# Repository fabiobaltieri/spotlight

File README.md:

# Spotlight

BLE enabled headlamp and mod boards.

## License (firmware, bootloader, ciq-app)

This program is free software: you can redistribute it and/or modify
it under the terms of the GNU General Public License as published by
the Free Software Foundation, either version 3 of the License, or
(at your option) any later version.

## License (hardware)

Hardware files are licensed under a
Creative Commons Attribution-ShareAlike 4.0 International License.

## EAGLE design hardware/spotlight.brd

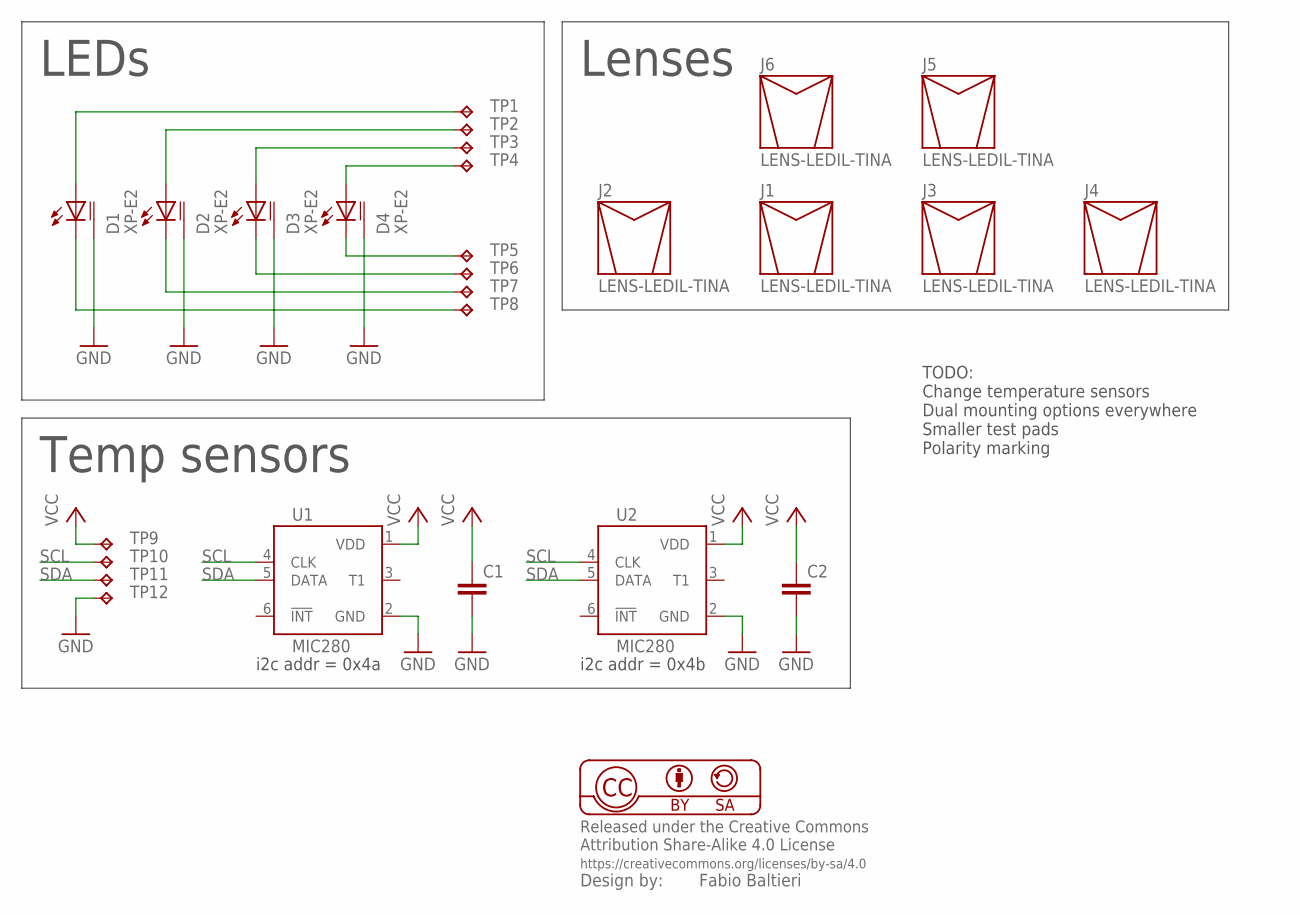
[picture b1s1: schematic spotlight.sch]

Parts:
C1, C2: C0603; 0603
D1, D2, D3, D4: XP-E2; CREE_XPE
J1, J2, J3, J4, J5, J6: LENS-LEDIL-TINA; LEDIL-TINA
TP1, TP2, TP3, TP4, TP5, TP6, TP7, TP8: TPTP18R; TP18R
TP9, TP10, TP11, TP12: TPTP14R; TP14R
U1, U2: MIC280; SOT23-6L

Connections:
GND: C1.2, C2.2, D1.TH, D2.TH, D3.TH, D4.TH, TP12.TP, U1.2 (GND), U2.2 (GND)
unnamed: D4.K (C), TP5.TP
unnamed: D3.K (C), TP6.TP
unnamed: D2.K (C), TP7.TP
unnamed: D1.K (C), TP8.TP
unnamed: D4.A, TP4.TP
unnamed: D3.A, TP3.TP
unnamed: D2.A, TP2.TP
unnamed: D1.A, TP1.TP
SCL: TP10.TP, U1.4 (CLK), U2.4 (CLK)
SDA: TP11.TP, U1.5 (DATA), U2.5 (DATA)
VCC: C1.1, C2.1, TP9.TP, U1.1 (VDD), U2.1 (VDD)

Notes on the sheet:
Lenses
LEDs
Temp sensors
i2c addr = 0x4a
i2c addr = 0x4b
TODO: Change temperature sensors Dual mounting options everywhere Smaller test pads Polarity marking

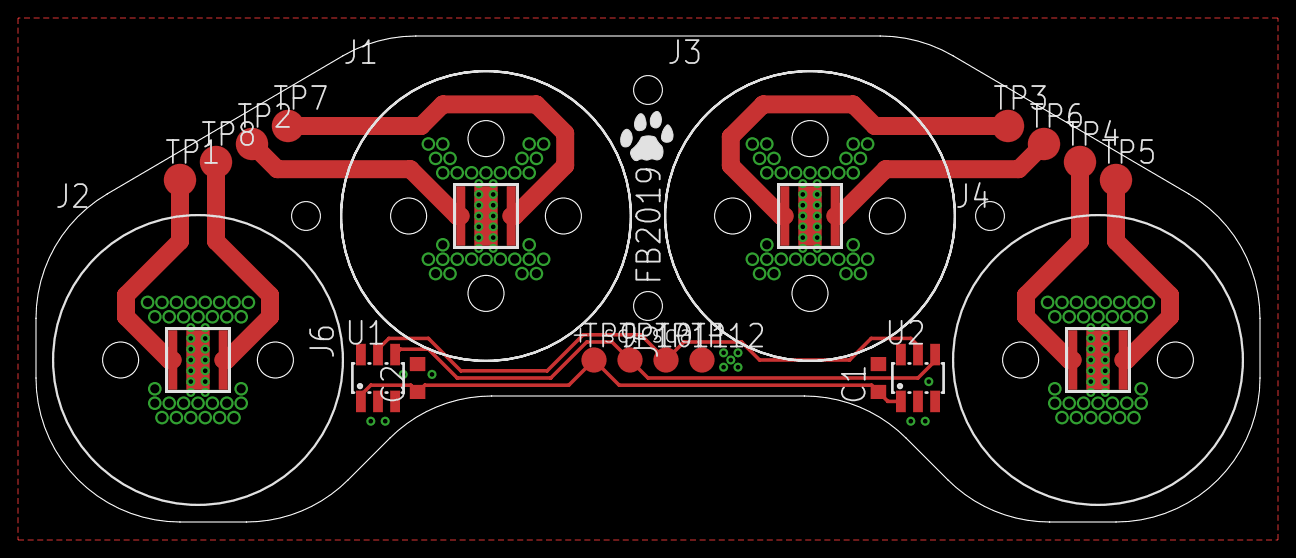
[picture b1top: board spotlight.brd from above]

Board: 2 copper layers, 68.0 x 27.0 mm, 27 parts (0 on the bottom side), 12 nets.

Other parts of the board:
U$1: CAT-L

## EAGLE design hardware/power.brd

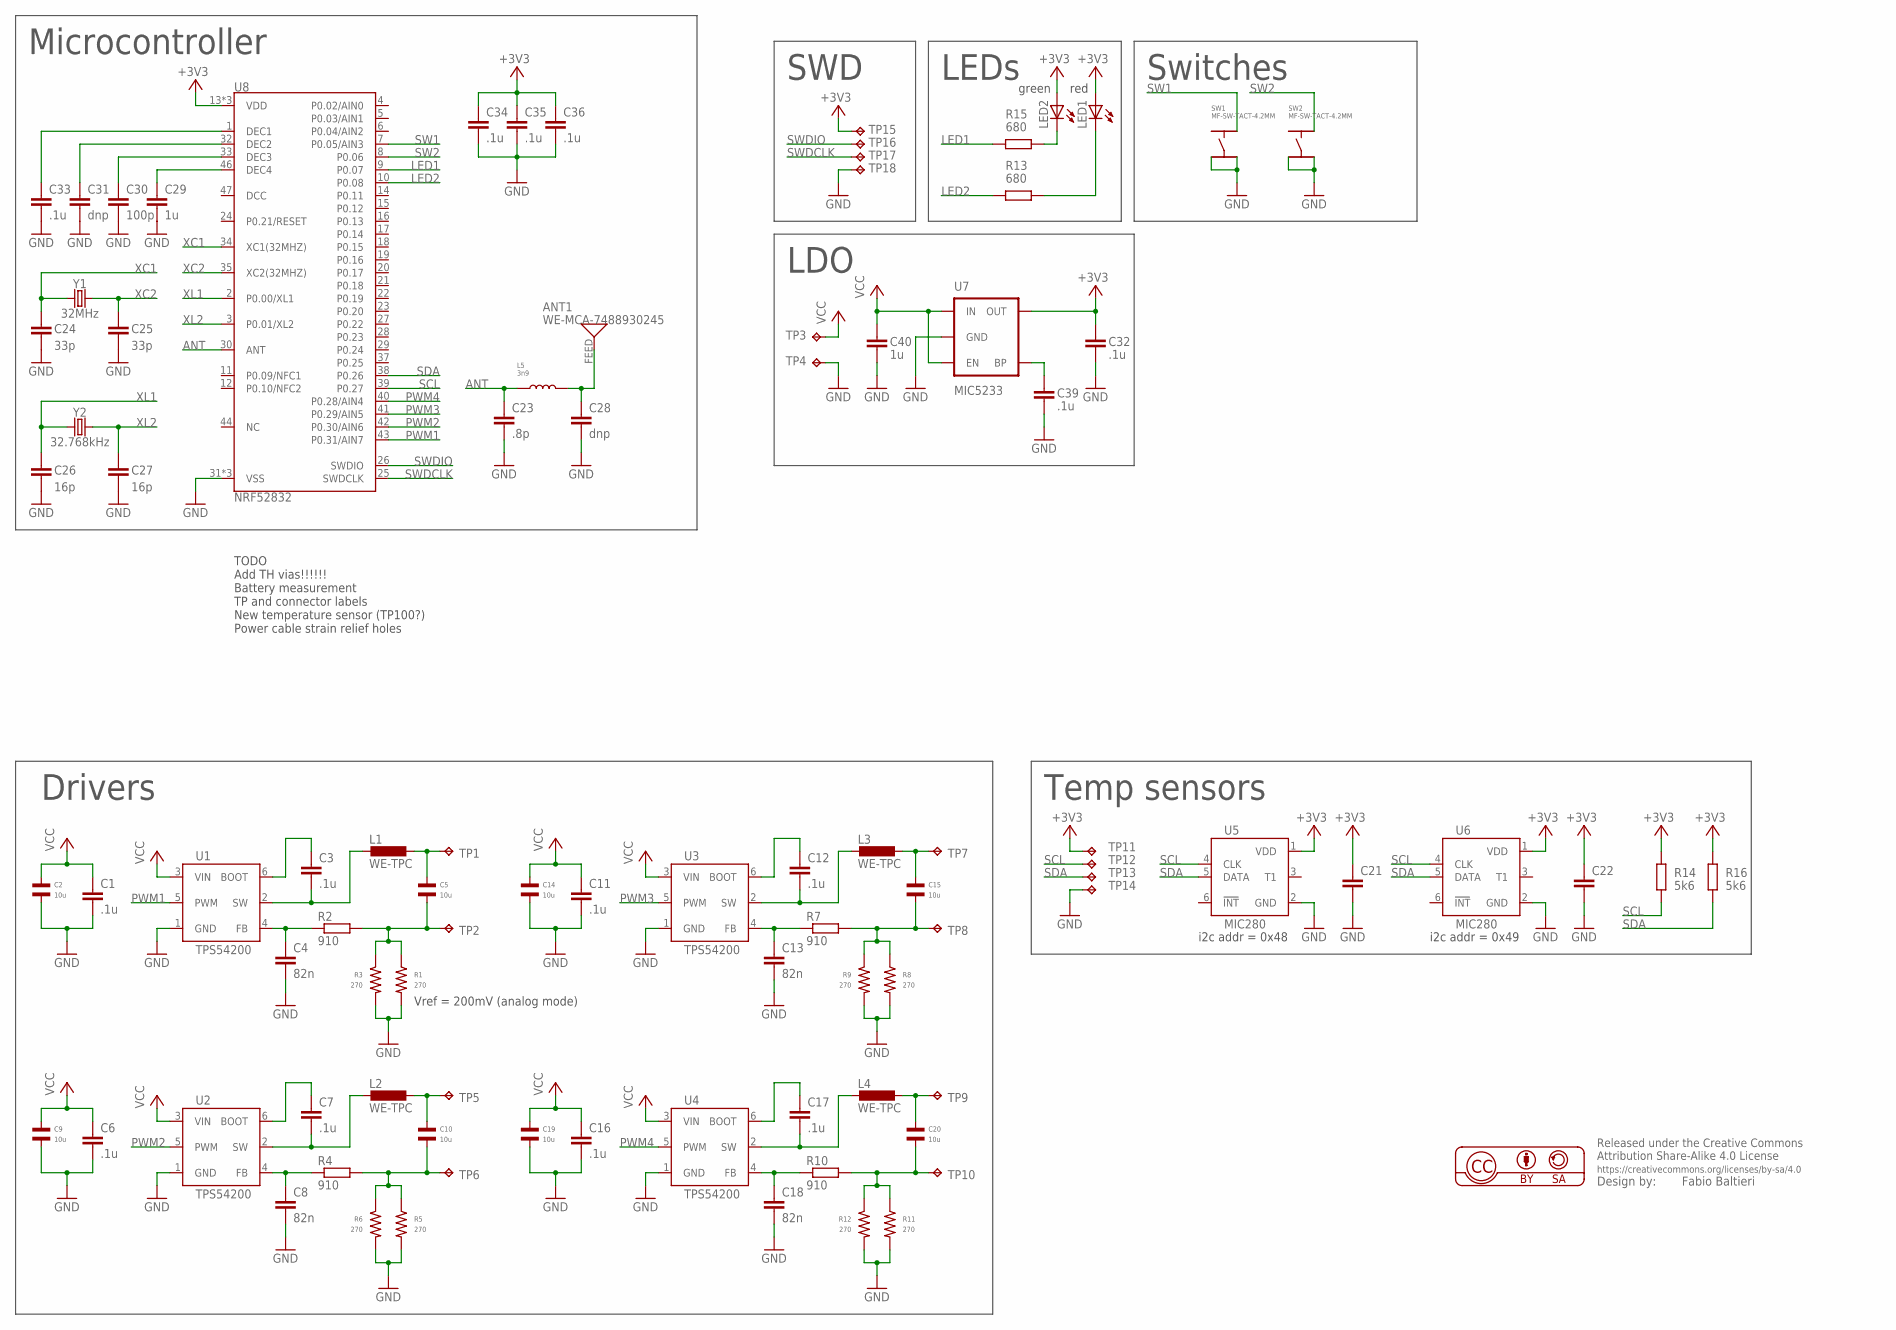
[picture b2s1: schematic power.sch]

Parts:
ANT1: WE-MCA-7488930245; WE-MCA
C1, C3, C6, C7, C11, C12, C16, C17, C32, C33, C34, C35, C36, C39: .1u; 0603
C2, C5, C9, C10, C14, C15, C19, C20: 10u; C1206
C4, C8, C13, C18: 82n; 0603
C21, C22: C0603; 0603
C23: .8p; 0603
C24, C25: 33p; 0603
C26, C27: 16p; 0603
C28, C31: dnp; 0603
C29, C40: 1u; 0603
C30: 100p; 0603
L1, L2, L3, L4: WE-TPC; WE-TPC_INDUCTOR
L5: 3n9; L0603
LED1, LED2: LEDSML0805; SML0805
R1, R3, R5, R6, R8, R9, R11, R12: 270; R0805
R2, R4, R7, R10: 910; 0603
R13, R15: 680; 0603
R14, R16: 5k6; 0603
SW1, SW2: MF-SW-TACT-4.2MM; TACT4.2MM
TP1, TP2, TP3, TP4, TP5, TP6, TP7, TP8, TP9, TP10: TPTP18R; TP18R
TP11, TP12, TP13, TP14: TPTP14R; TP14R
TP15, TP16, TP17, TP18: TPTP12R; TP12R
U1, U2, U3, U4: TPS54200; SOT23-6L
U5, U6: MIC280; SOT23-6L
U7: MIC5233; SOT23-5
U8: NRF52832; QFN48-6X6MM
Y1: 32MHz; CRYSTAL-SMD-3.2X2.5MM
Y2: 32.768kHz; CRYSTAL-SMD-3.2X1.5MM

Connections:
+3V3: C21.1, C22.1, C32.1, C34.1, C35.1, C36.1, LED1.A, LED2.A, R14.1, R16.1, TP11.TP, TP15.TP, U5.1 (VDD), U6.1 (VDD), U7.5 (OUT), U8.13 (VDD), U8.36 (VDD), U8.48 (VDD)
ANT: C23.1, L5.P$1, U8.30 (ANT)
GND: C1.2, C2.P$2, C4.2, C6.2, C8.2, C9.P$2, C11.2, C13.2, C14.P$2, C16.2, C18.2, C19.P$2, C21.2, C22.2, C23.2, C24.2, C25.2, C26.2, C27.2, C28.2, C29.2, C30.2, C31.2, C32.2, C33.2, C34.2, C35.2, C36.2, C39.2, C40.2, R1.P$2, R3.P$2, R5.P$2, R6.P$2, R8.P$2, R9.P$2, R11.P$2, R12.P$2, SW1.P$3, SW1.P$4, SW2.P$3, SW2.P$4, TP4.TP, TP14.TP, TP18.TP, U1.1 (GND), U2.1 (GND), U3.1 (GND), U4.1 (GND), U5.2 (GND), U6.2 (GND), U7.2 (GND), U8.31 (VSS), U8.45 (VSS), U8.EP (VSS)
LED1: R15.2, U8.9 (P0.07)
LED2: R13.2, U8.10 (P0.08)
unnamed: C3.2, L1.P$1 (1), U1.2 (SW)
unnamed: C3.1, U1.6 (BOOT)
unnamed: C5.P$1, L1.P$2 (2), TP1.TP
unnamed: C4.1, R2.1, U1.4 (FB)
unnamed: C5.P$2, R1.P$1, R2.2, R3.P$1, TP2.TP
unnamed: C7.2, L2.P$1 (1), U2.2 (SW)
unnamed: C7.1, U2.6 (BOOT)
unnamed: C8.1, R4.1, U2.4 (FB)
unnamed: C10.P$2, R4.2, R5.P$1, R6.P$1, TP6.TP
unnamed: C10.P$1, L2.P$2 (2), TP5.TP
unnamed: C12.2, L3.P$1 (1), U3.2 (SW)
unnamed: C12.1, U3.6 (BOOT)
unnamed: C13.1, R7.1, U3.4 (FB)
unnamed: C15.P$2, R7.2, R8.P$1, R9.P$1, TP8.TP
unnamed: C15.P$1, L3.P$2 (2), TP7.TP
unnamed: C17.2, L4.P$1 (1), U4.2 (SW)
unnamed: C17.1, U4.6 (BOOT)
unnamed: C18.1, R10.1, U4.4 (FB)
unnamed: C20.P$2, R10.2, R11.P$1, R12.P$1, TP10.TP
unnamed: C20.P$1, L4.P$2 (2), TP9.TP
unnamed: LED1.C, R13.1
unnamed: ANT1.FEED, C28.1, L5.P$2
unnamed: LED2.C, R15.1
unnamed: C29.1, U8.46 (DEC4)
unnamed: C30.1, U8.33 (DEC3)
unnamed: C31.1, U8.32 (DEC2)
unnamed: C33.1, U8.1 (DEC1)
unnamed: C39.1, U7.4 (BP)
PWM1: U1.5 (PWM), U8.43 (P0.31/AIN7)
PWM2: U2.5 (PWM), U8.42 (P0.30/AIN6)
PWM3: U3.5 (PWM), U8.41 (P0.29/AIN5)
PWM4: U4.5 (PWM), U8.40 (P0.28/AIN4)
SCL: R14.2, TP12.TP, U5.4 (CLK), U6.4 (CLK), U8.39 (P0.27)
SDA: R16.2, TP13.TP, U5.5 (DATA), U6.5 (DATA), U8.38 (P0.26)
SW1: SW1.P$2, U8.7 (P0.05/AIN3)
SW2: SW2.P$2, U8.8 (P0.06)
SWDCLK: TP17.TP, U8.25 (SWDCLK)
SWDIO: TP16.TP, U8.26 (SWDIO)
VCC: C1.1, C2.P$1, C6.1, C9.P$1, C11.1, C14.P$1, C16.1, C19.P$1, C40.1, TP3.TP, U1.3 (VIN), U2.3 (VIN), U3.3 (VIN), U4.3 (VIN), U7.1 (IN), U7.3 (EN)
XC1: C24.1, U8.34 (XC1(32MHZ)), Y1.1
XC2: C25.1, U8.35 (XC2(32MHZ)), Y1.3 (2)
XL1: C26.1, U8.2 (P0.00/XL1), Y2.P$1 (1)
XL2: C27.1, U8.3 (P0.01/XL2), Y2.P$2 (2)

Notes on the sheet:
LDO
Drivers
Temp sensors
LEDs
Microcontroller
SWD
Switches
red
green
Vref = 200mV (analog mode)
TODO Add TH vias!!!!!! Battery measurement TP and connector labels New temperature sensor (TP100?) Power cable strain relief holes
i2c addr = 0x48
i2c addr = 0x49

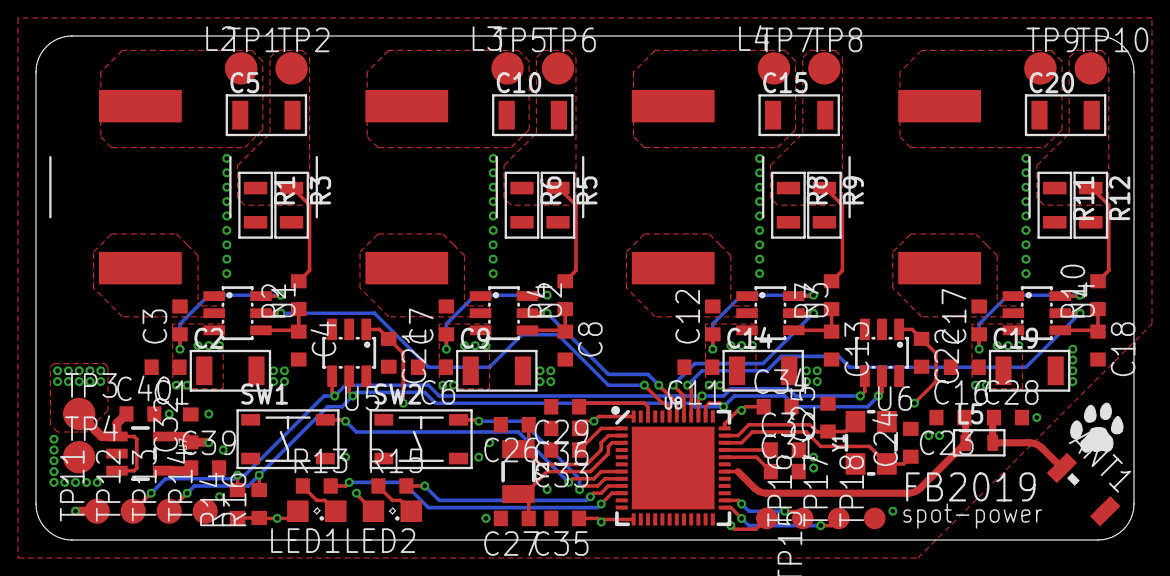
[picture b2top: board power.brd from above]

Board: 4 copper layers, 61.0 x 28.0 mm, 93 parts (0 on the bottom side), 48 nets.

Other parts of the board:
U$1: CAT-L

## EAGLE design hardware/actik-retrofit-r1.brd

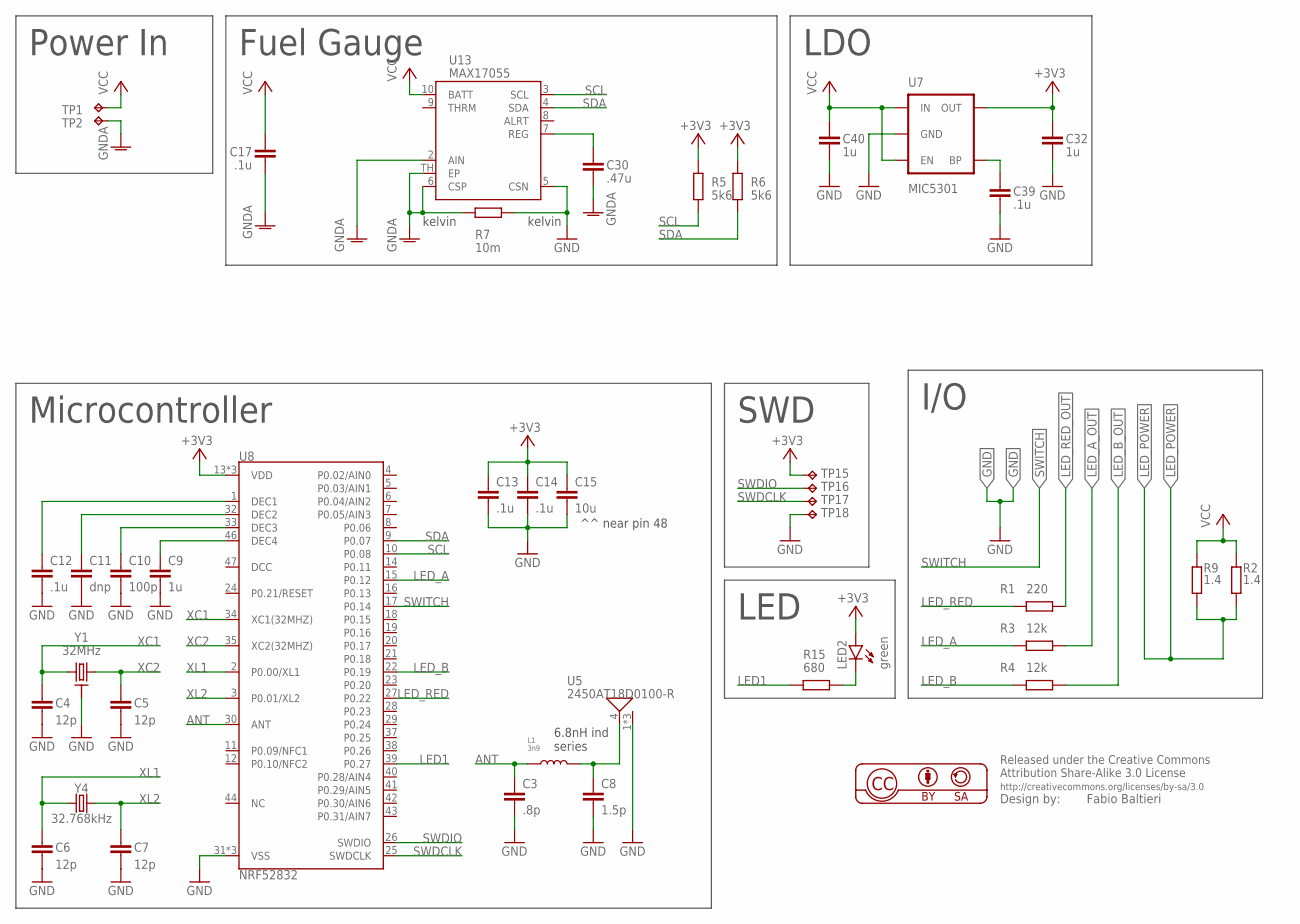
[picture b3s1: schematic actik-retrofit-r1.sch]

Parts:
C3: .8p; 0603
C4, C5, C6, C7: 12p; 0603
C8: 1.5p; 0603
C9, C32, C40: 1u; 0603
C10: 100p; 0603
C11: dnp; 0603
C12, C13, C14, C17, C39: .1u; 0603
C15: 10u; 0603
C30: .47u; 0603
L1: 3n9; L0603
LED2: green; SML0805
R1: 220; 0603
R2, R9: 1.4; R3225
R3, R4: 12k; 0603
R5, R6: 5k6; 0603
R7: 10m; 0603
R15: 680; 0603
TP1, TP2: TPPAD1-13; P1-13
TP15, TP16, TP17, TP18: TPTP10R; TP10R
U5: 2450AT18D0100-R
U7: MIC5301; SOT23-5
U8: NRF52832; QFN48-6X6MM
U13: MAX17055; TDFN10-2X2.5
Y1: 32MHz; XTAL-2X1.6
Y4: 32.768kHz; CRYSTAL-SMD-3.2X1.5MM

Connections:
+3V3: C13.1, C14.1, C15.1, C32.1, LED2.A, R5.1, R6.1, TP15.TP, U7.5 (OUT), U8.13 (VDD), U8.36 (VDD), U8.48 (VDD)
ANT: C3.1, L1.P$1, U8.30 (ANT)
GND: C3.2, C4.2, C5.2, C6.2, C7.2, C8.2, C9.2, C10.2, C11.2, C12.2, C13.2, C14.2, C15.2, C32.2, C39.2, C40.2, R7.1, TP18.TP, U5.1 (GND), U5.2 (GND), U5.3 (GND), U7.2 (GND), U8.31 (VSS), U8.45 (VSS), U8.EP (VSS), U13.5 (CSN), Y1.2 (GND), Y1.4 (GND)
GNDA: C17.2, C30.2, R7.2, TP2.TP, U13.2 (AIN), U13.6 (CSP), U13.TH (EP)
LED1: R15.2, U8.39 (P0.27)
LED_A: R3.2, U8.15 (P0.12)
LED_A_OUT: R3.1
LED_B: R4.2, U8.22 (P0.19)
LED_B_OUT: R4.1
LED_POWER: R2.2, R9.2
LED_RED: R1.2, U8.27 (P0.22)
LED_RED_OUT: R1.1
unnamed: C8.1, L1.P$2, U5.4 (FEED)
unnamed: C9.1, U8.46 (DEC4)
unnamed: C10.1, U8.33 (DEC3)
unnamed: C11.1, U8.32 (DEC2)
unnamed: C12.1, U8.1 (DEC1)
unnamed: LED2.C, R15.1
unnamed: C39.1, U7.4 (BP)
unnamed: C30.1, U13.7 (REG)
SCL: R5.2, U8.10 (P0.08), U13.3 (SCL)
SDA: R6.2, U8.9 (P0.07), U13.4 (SDA)
SWDCLK: TP17.TP, U8.25 (SWDCLK)
SWDIO: TP16.TP, U8.26 (SWDIO)
SWITCH: U8.17 (P0.14)
VCC: C17.1, C40.1, R2.1, R9.1, TP1.TP, U7.1 (IN), U7.3 (EN), U13.10 (BATT)
XC1: C4.1, U8.34 (XC1(32MHZ)), Y1.1
XC2: C5.1, U8.35 (XC2(32MHZ)), Y1.3 (2)
XL1: C6.1, U8.2 (P0.00/XL1), Y4.P$1 (1)
XL2: C7.1, U8.3 (P0.01/XL2), Y4.P$2 (2)

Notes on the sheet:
LDO
LED
SWD
I/O
Power In
Microcontroller
^^ near pin 48
Fuel Gauge
kelvin
6.8nH ind series

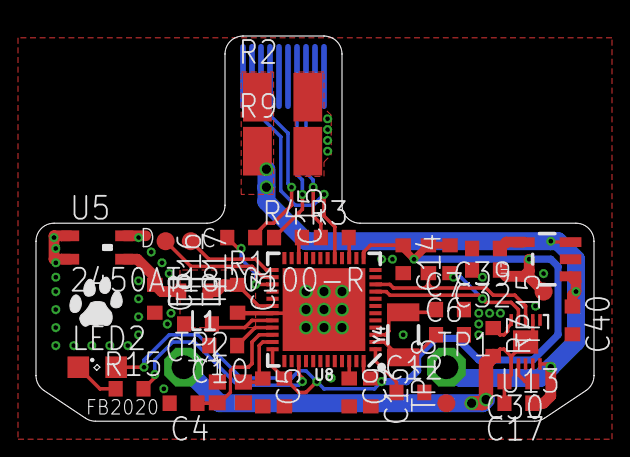
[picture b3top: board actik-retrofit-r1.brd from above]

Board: 2 copper layers, 31.0 x 21.4 mm, 42 parts (0 on the bottom side), 26 nets.

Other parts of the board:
U$1: CAT-L

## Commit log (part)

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2019-02-19 spotlight: rev0
2019-02-19 power: wip
2019-05-04 power: power routed, control placed
2019-07-02 power: r0?
2019-09-15 power: schematic refactoring?
2019-09-18 power: few assembly notes
2019-10-22 rename hw -> hardware
2019-10-23 fw: it blinks
2019-10-23 fw: bunch of init stuff and buttons and LEDs working
2019-10-23 fw: style cleanups
2019-10-23 fw: add pwm support
2019-10-24 fw: add i2c support
2019-10-24 fw: a timer, just for fun
2019-10-27 remote: initial firmware
2019-10-27 fw: add power board ping mapping
2019-10-27 fw: add config for power led polarity
2019-10-27 fw: add utils module, ant dump function
2019-10-27 fw: move pwm setup on its own function
2019-10-27 fw: implement rx and tx stubs
2019-10-27 fw: move levels at the top
2019-10-27 fw: mask few more known ant codes
2019-10-27 fw: actually set pwm levels
2019-10-27 fw: load tx on previous tx sent (for now)
2019-10-27 fw: add a backend define to control logging
2019-10-27 fw: add a debug log line for tx collision
2019-10-28 ciq: add searching indication
2019-10-28 remote: only blink on tx events
2019-10-28 fw: add light change smoothing
2019-10-28 fw: add few comments on the timer start code
2019-10-28 fw: drop the m_ prefix from twi
    No idea what it was for anyway.
2019-10-28 fw: pwm_update, reverse the return logic
2019-10-28 fw: movw temp i2c code to a separate driver file
2019-10-28 fw: move timer defs at the top
2019-10-30 fw: add missing (void) in timer_init
2019-10-30 fw: shuffle init around, twi before timer
2019-10-30 fw: add an hello start sequence
2019-10-30 fw: rename levels to tgt_levels
2019-10-30 fw: initial mode switching code
    TODO: smarter fallback strategy
2019-10-30 fw: initial telemetry code
2019-10-30 ciq: add timer state change stubs
2019-10-30 ciq: add initial telemetry rx code
2019-10-30 rename maximum to high and H, beams are !
2019-10-30 ciq: comment out ant debugging code
2019-10-30 fw: take input from both switches
2019-10-31 ciq: implement sendback for auto mode
2019-10-31 fw: drop useless memset (or should I drop the explicit loads?)
2019-10-31 fw: split out apply state
2019-10-31 fw: skip tx load if payload has not changed
2019-10-31 fw: add a level debug print
2019-10-31 fw: disable remote support by default
2019-10-31 fw: halve the spot on mid mode
2019-11-01 remote: add missing linker script
2019-11-01 add a .gitignore file
2019-11-01 fw: config: single define for testing on pca10040
2019-11-01 fw: add a conditional for remote channel reopen
2019-11-01 fw: use led 0 to indicate remote status
2019-11-01 fw: propagate remote data
2019-11-01 fw: drop few silly p_ pointer prefixes
2019-11-01 fw: add saadc support and periodic sampling
2019-11-02 fw: move init things around to help startup troubleshooting
2019-11-02 fw: add battery voltage reporting (not quite percentage yet)
2019-11-04 ciq: add a Makefile
2019-11-04 ciq: allow dynamic device override
2019-11-04 fw: probe the internal temperature sensor for no good reason
2019-11-04 ciq: add telemetry logging in the fit file
2019-11-21 ciq: drop a space in the debug comment
2019-11-22 fw: decreae button delay to 2 seconds, reasons
2019-11-24 fw: Maximum? High!
2019-12-15 fw: Makefile: point to s212 v6.1.1
2019-12-15 fw: adjust high mode beam
2019-12-15 fw: blink on ant tx done
2019-12-15 fw: only use the two front sensor for temperature
    ...and still use the die sensor on the dev board.
2020-03-22 ciq: change idle delay to 20 secs
2020-03-22 ciq: change temp color slightly
2020-03-22 fw: add feature checks for remote, ext temp and pwm
2020-03-22 ciq: change sendback to react faster to record changes
2020-03-22 ciq: drop the 5V special case, who cares.
2020-03-22 fw: rework the target selection logic to have multiple choices
2020-03-22 ciq: show the device id for a second
2020-03-22 remote: target name and coding style fixes
2020-03-23 fw: enable timer v2 implementation
2020-04-07 fw/ciq: move data to a paginated format
2020-04-07 ciq: only set deviceNum on broadcast data
    ...it's null for channel event messages
2020-04-07 ciq: print only after setting deviceNum
2020-04-07 ciq: log channel open events
2020-04-07 ciq: switch upload data to page format as well
2020-04-07 fw: set slave remote channel transmission type to 0
2020-04-10 fW: use autogenerated device number
2020-04-13 hw: actik-retrofit: first candidate
2020-04-13 hw: actik-retrofit: sent to fab, r0
2020-04-14 ciq: reformat manifest for tabs
2020-04-18 hw: show inductor value on the antenna line
2020-04-19 Makefile: add era command, other cleanups
2020-05-24 bl: import pca10040 s132 secure bootloader
2020-05-24 bl: sort the targets in the Makefile
2020-05-24 bl: add board settings from the main firmware
2020-05-24 bl: clean error functions, use only one led
2020-05-24 fw: add a dfu flash target
2020-05-30 hw: actik: annotate the main decoupling cap
2020-06-02 ciq: drop unnecessary return from onStart and onStop
2020-06-09 hw: actik: change few R values
2020-06-11 ciq: add short string option
2020-06-11 fw: annotate tk-retrofit unused pins
2020-06-13 fw, bl: add actik retrofit pin mapping
2020-06-13 fw: make pwm period configurable
2020-06-13 fw: add a set of pwm levels for the actik
2020-06-13 fw: refactor remote out of main
2020-06-13 fw: clean few includes from main, define levels in state.h
2020-06-13 fw: clean up remote and telemetry includes
2020-06-13 fw: refactor levels out of main
2020-06-13 fw: drop stale ant debug macro from main
2020-06-14 fw: clean utils.c includes
2020-06-14 fw: move input out of main
2020-06-14 fw: system: minor refactoring, mainly ext temp handling
2020-06-14 fw: handle no PWM properly
2020-06-14 fw: change adc gain, get a bit more resolution
2020-06-14 fw: rename temp_tmr to sys_tmr
2020-06-14 fw: add auto-shutdown after 15 minutes
2020-06-16 fw: system: move get_max_temp close to the caller
2020-06-18 fw: replace targets defs to #ifdefs
2020-06-18 fw: system: simplify update_temp
2020-06-18 fw: system: add a reserve mode on 0% SOC
2020-06-19 bl: update APIs to SDK v17.0.0
2020-06-22 hw: add actik-retrofit-r1
2020-06-22 hw: actik-r1: change a polygon, few couple nets width
2020-07-12 hw: change few values
2020-07-27 hw: actik-r1 set red led res value
2020-07-27 fw: switch actik pin map to r1
2020-07-28 ciq: extend sign with shift instead of check
2020-07-28 ciq: ant: add tte
2020-07-28 ciq: display tte instead of temperature
2020-07-28 fw: add TARGET_HAS_FUEL_GAUGE definition
    Just shut off the adc for the moment.
2020-07-28 fw: add max17055 driver and soc/tte implementation
2020-08-04 fw: exclude the max17055 code if not used
2020-08-06 fw: system: declare tte at the function start
2020-08-06 fw: change few function names for coherency
2020-08-15 fw: enter reserve based on cell voltage on actik
2020-08-17 fw: switch to twim, define twi instance externally
2020-08-22 ciq: only initialize the fit fields after seeing the device the first time
2020-09-14 ciq: update key path
2020-09-18 fw,bl: update to SDK 17.0.2
2020-09-25 hw: actik-r1: annotate schematics for antenna tuning values
2020-09-25 fw,bl,ciq: switch telemetry to chan 58 devtype 7b and 7c
2020-09-28 ciq: manifest: new UUID
2020-09-28 ciq: Makefile: update app id
2020-10-08 fw: telemetry: blink the led with a timer, remove the delay
2020-11-13 fw: system: add battery level blinking indicator
2021-01-30 config: default to build for actik
2021-01-30 levels: set high strenght high drive on the red led pin
2021-02-14 input: add missing include
2021-02-27 Add a README file
2021-04-02 hw: drop tk-retrofit files
2021-04-02 update libraries and licence text
2021-04-13 bl: build for actik by default
2021-04-13 ciq-app: add a ant data debug print, commented out by default
2021-05-19 bl,fw: drop -f from dfu ble commands
2021-07-27 fw: telemetry, remote: use local channel variable
2021-07-28 ciq-app: split AntDevice device specific data out
2021-08-20 fw: drop useless static qualifier from device_number
2021-08-30 fw: report calculated ocv rather than actual voltage
2021-10-26 ciq-app: print dc
2022-05-25 fw: add verify to nrfjprog
2022-06-01 ciq-app: default to fr955
2022-06-22 ciq-app: increase reopen delay to 60 seconds
2022-07-08 gitignore: ignore zephyr build directory
2022-07-09 prj.conf: add more stuff in prj.conf
2022-07-09 zfw: enable stack info
2022-07-09 zfw: add flash_mcuboot
2022-07-09 zfw: setup fw management for ota
2022-07-12 zfw: adjust few partition sizes
2022-07-12 zfw: fix few wrong mcumgr commands
2022-07-12 zfw: make ota script a bit more automatic
2022-07-22 zfw: change zephyr.h in kernel.h
2022-07-22 zfw: add button
2022-07-23 zfw: button: drop empty line
2022-07-23 zfw: main: sync using a k_timer
2022-07-23 zfw: initial system.c
2022-07-24 zfw: simplify dts, add error handling, button event hack
2022-07-24 zfw: add device state
2022-07-24 zfw: add temp sensor reading
2022-07-24 zfw: give button and system thread a bit more stack
2022-07-24 zfw: add few missing static qualifiers
2022-07-24 zfw: add levels hello
2022-07-24 zfw: main: always blink if not shutting down
2022-07-24 zfw: update ble bas soc
2022-07-24 zfw: drop max17055 dts label
2022-07-24 zfw: add dc update code
2022-07-25 zfw: mystery gpio pin interrupt flag now works... go figure
2022-07-25 zfw: drop control to 3 LEDs
2022-07-25 zfw: fix up timestamp type
2022-07-25 zfw: add level control, it's a headlamp again
2022-07-25 zfw: no more printk, use LOG_ macros
2022-07-26 zfw: ble: add a spotlight profile
2022-07-26 zfw: add nrf52dk dts overlay
2022-07-27 zfw: rename uuid to STATUS
2022-07-27 zfw: only send notifications when enabled
2022-07-27 zfw: add a warning when building with the nrf52dk overlay
2022-07-27 zfw: add a command line reference to the overlay
2022-07-27 zfw: implement auto control
2022-07-27 zfw: swap mode/level nibbles
2022-07-27 zfw: redefine MODE_SHUTDOWN to 0xf
2022-07-27 zfw: top up tte to 0xff
2022-07-27 zfw: enable stack initialization
2022-07-27 zfw: increase log thread stack size
2022-08-12 ciq-app-ble: initial import
2022-08-21 zfw: change temp dev to DEVICE_DT_GET_ONE
2022-09-03 ciq-app-ble: refactor BleDevice and Spotlight
2022-09-03 ciq-app-ble: refactor some stuff out of DataField into Spotlight
2022-09-03 ciq-app-ble: rework ble connection logic, add idling
2022-09-11 zfw: drop few labels
2022-11-06 zfw: add dump_data_ble.py
2022-12-08 zfw: fix wrong project name
2022-12-08 zfw: ble: fix mgmt include paths
2023-01-08 zfw: update the ble config symbols and apis
2023-01-08 zfw: disable mcumgr auto bt init, initialize manually
2023-01-23 zfw: drop few headers
2023-02-22 fw: fix config for zephyr v3.3
2023-03-09 fw: add more mcumgr configs
2023-03-14 fw: add flash_ota.py, drop flash_ota
2023-04-14 fw: change SYS_INIT function arg to void
2023-04-14 fw: ble: tweak bt connection parameters
2023-04-26 make the label uppercase
2023-04-26 Makefile: set the app id
2023-05-03 drop the old ANT base code base
2023-05-03 fw, ciq-app: rename to firmware and ciq-app
2023-05-03 fw: fix key path
2023-05-13 fw: change main to return int
2023-05-30 fw: set i2c to 400khz
2023-05-30 fw: rename system to sys
2023-08-04 fw: add missing include prefix
2023-08-04 fw: use sys_poweroff
2023-08-07 fw: switch to gpio-keys
2023-08-11 fw: update input callback macro name
2023-08-11 fw: use NRF_DT_GPIOS_TO_PSEL
2023-08-11 update gitignore file
2023-08-11 fw: add a west manifest
2023-08-12 fw: use sensor_sample_fetch_chan
2023-08-12 build: use working-directory
2023-09-10 fw: dump_data_ble: sync after print
2023-09-19 build: use the common zephyr setup action
2023-09-20 build: only download arm-zephyr-eabi
2023-10-09 fw: update the button wakeup api to not use the hal
2023-10-25 build: use the key from github secrets
2023-11-02 fw: drop a redundant config option
2023-11-10 fw: more header cleanups
2023-11-14 fw: start ble last
2023-11-24 fw: drop few redundant options
2023-11-26 fw: move LOG_MODULE_REGISTER after the headers
2023-11-29 fw: dwork variable rename
2024-01-20 build: use the official action
2024-01-29 fw: fix a double promotion warning
2024-07-08 fw: set sense-edge-mask
2024-07-08 fw: reduce ble adv period
2024-07-08 fw: change shutdown delay to 30 minutes
2024-07-31 fw: input api update
2024-09-20 fw: drop bt deprecated option
2025-02-05 fw: drop --softreset

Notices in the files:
parts and their libraries:
SparkFun-PowerIC: Licensing: CC v3.0 Share-Alike You are welcome to use this library for commercial purposes.
SparkFun-RF: Licensing: Creative Commons ShareAlike 4.0 International - https://creativecommons.org/licenses/by-sa/4.0
balto: Released under the Creative Commons
